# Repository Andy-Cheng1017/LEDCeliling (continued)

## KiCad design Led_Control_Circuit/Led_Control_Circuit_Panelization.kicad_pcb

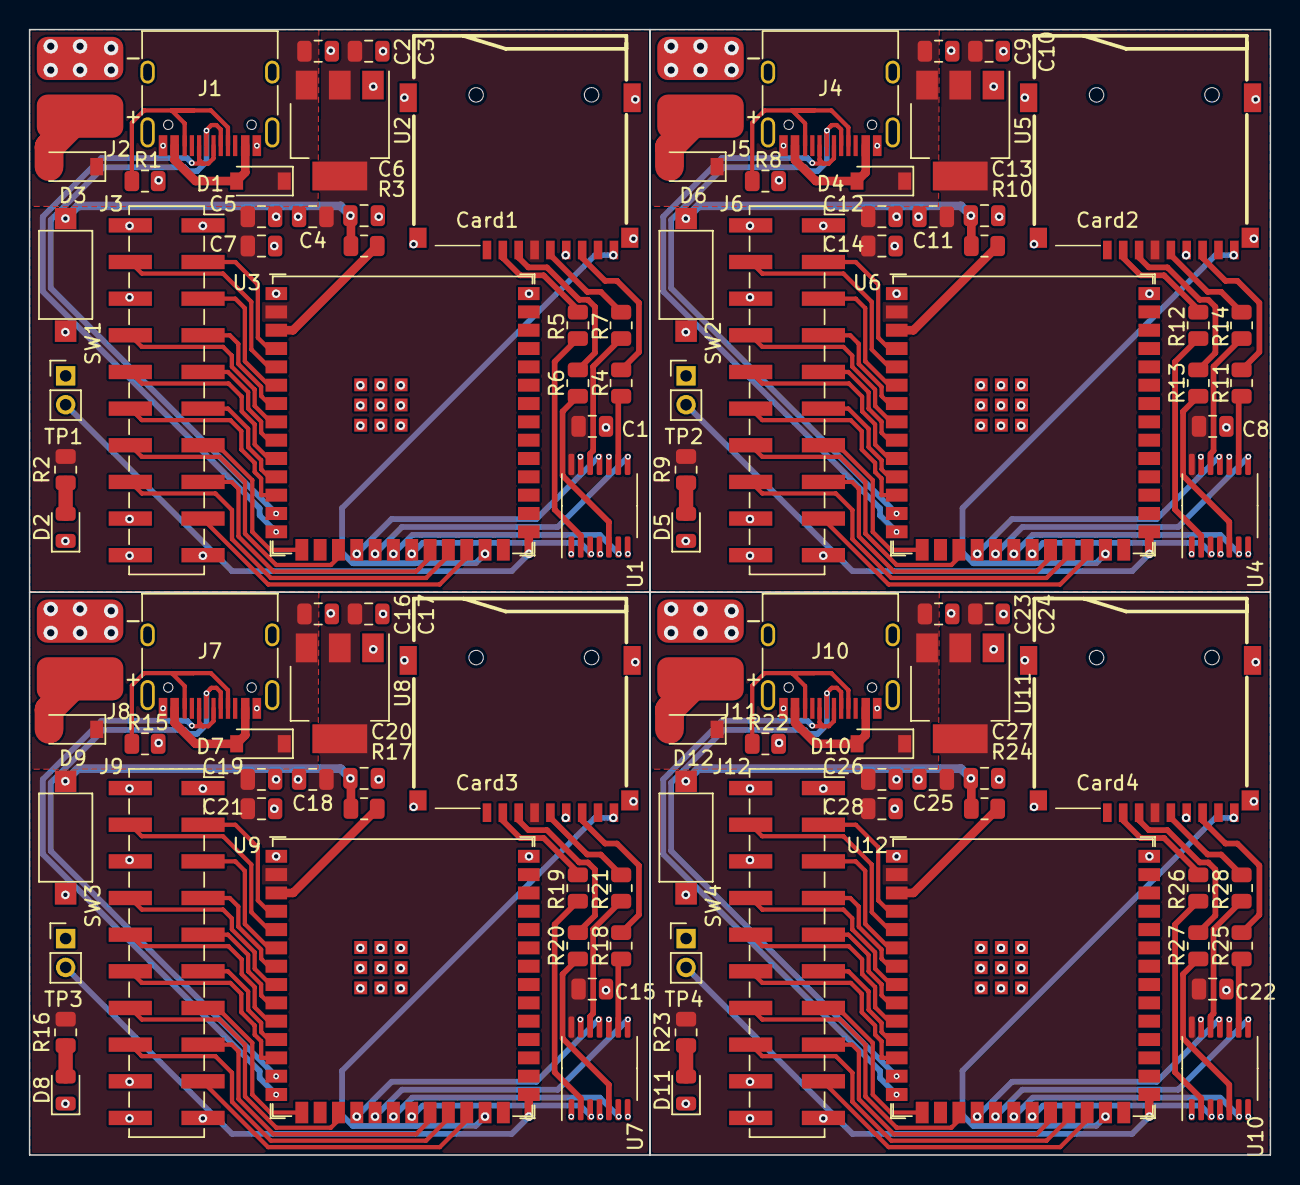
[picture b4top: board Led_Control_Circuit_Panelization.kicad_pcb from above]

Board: 2 copper layers, 86.0 x 78.0 mm, 104 parts (0 on the bottom side), 39 nets.

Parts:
C1, C7, C8, C14, C15, C21, C22, C28: 0.1u; C_0805_2012Metric
C2, C3, C5, C6, C9, C10, C12, C13, C16, C17, C19, C20, C23, C24, C26, C27: 1u; C_0805_2012Metric
C4, C11, C18, C25: 10u; C_0805_2012Metric
Card1, Card2, Card3, Card4: TF-01A; TF-SMD_TF-01A
D1, D3, D4, D6, D7, D9, D10, D12: 1N5819HW; D_SOD-123
D2, D5, D8, D11: LED0805; LED_0805_2012Metric
J1, J4, J7, J10: USB_C_Receptacle_USB2.0; USB_C_Receptacle_HRO_TYPE-C-31-M-12
J2, J5, J8, J11: Conn_01x02; Battery
J3, J6, J9, J12: Conn_01x20; PinSocket_2x10_P2.54mm_Vertical_SMD
R1, R8, R15, R22: 5.1K; R_0805_2012Metric
R2, R9, R16, R23: 1k; R_0805_2012Metric
R3, R10, R17, R24: 1K; R_0805_2012Metric
R4, R5, R6, R7, R11, R12, R13, R14, R18, R19, R20, R21, R25, R26, R27, R28: 3.3K; R_0805_2012Metric
SW1, SW2, SW3, SW4: SW_Push; SW_SPST_CK_RS282G05A3
TP1, TP2, TP3, TP4: TestPoint_2Pole; PinHeader_1x02_P2.00mm_Vertical
U1, U4, U7, U10: 74LVC125; TSSOP-14_4.4x5mm_P0.65mm
U2, U5, U8, U11: AMS1117-3.3; SOT-223-3_TabPin2
U3, U6, U9, U12: ESP32-S3-WROOM-1; ESP32-S3-WROOM-1U

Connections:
+3.3V: C1.1, C3.1, C4.1, C5.1, C7.1, C8.1, C10.1, C11.1, C12.1, C14.1, C15.1, C17.1, C18.1, C19.1, C21.1, C22.1, C24.1, C25.1, C26.1, C28.1, Card1.4 (VDD), Card2.4 (VDD), Card3.4 (VDD), Card4.4 (VDD), R2.2, R9.2, R16.2, R23.2, U1.14 (VCC), U2.2 (VO), U3.2 (3V3), U4.14 (VCC), U5.2 (VO), U6.2 (3V3), U7.14 (VCC), U8.2 (VO), U9.2 (3V3), U10.14 (VCC), U11.2 (VO), U12.2 (3V3)
+5V: C2.1, C9.1, C16.1, C23.1, D1.1 (K), D3.1 (K), D4.1 (K), D6.1 (K), D7.1 (K), D9.1 (K), D10.1 (K), D12.1 (K), U2.3 (VI), U5.3 (VI), U8.3 (VI), U11.3 (VI)
/A: J3.11, J6.11, J9.11, J12.11, U3.11 (GPIO18/U1RXD/ADC2_CH7/CLK_OUT3), U6.11 (GPIO18/U1RXD/ADC2_CH7/CLK_OUT3), U9.11 (GPIO18/U1RXD/ADC2_CH7/CLK_OUT3), U12.11 (GPIO18/U1RXD/ADC2_CH7/CLK_OUT3)
/B: J3.12, J6.12, J9.12, J12.12, U3.12 (GPIO8/TOUCH8/ADC1_CH7/SUBSPICS1), U6.12 (GPIO8/TOUCH8/ADC1_CH7/SUBSPICS1), U9.12 (GPIO8/TOUCH8/ADC1_CH7/SUBSPICS1), U12.12 (GPIO8/TOUCH8/ADC1_CH7/SUBSPICS1)
/B1: J3.5, J6.5, J9.5, J12.5, U3.6 (GPIO6/TOUCH6/ADC1_CH5), U6.6 (GPIO6/TOUCH6/ADC1_CH5), U9.6 (GPIO6/TOUCH6/ADC1_CH5), U12.6 (GPIO6/TOUCH6/ADC1_CH5)
/B2: J3.9, J6.9, J9.9, J12.9, U3.9 (GPIO16/U0CTS/ADC2_CH5/XTAL_32K_NH5), U6.9 (GPIO16/U0CTS/ADC2_CH5/XTAL_32K_NH5), U9.9 (GPIO16/U0CTS/ADC2_CH5/XTAL_32K_NH5), U12.9 (GPIO16/U0CTS/ADC2_CH5/XTAL_32K_NH5)
/C: J3.13, J6.13, J9.13, J12.13, U3.15 (GPIO3/TOUCH3/ADC1_CH2), U6.15 (GPIO3/TOUCH3/ADC1_CH2), U9.15 (GPIO3/TOUCH3/ADC1_CH2), U12.15 (GPIO3/TOUCH3/ADC1_CH2)
/CD: Card1.9 (CD), Card2.9 (CD), Card3.9 (CD), Card4.9 (CD), U3.25 (GPIO48/SPICLK_N/SUBSPICLK_N_DIFF), U6.25 (GPIO48/SPICLK_N/SUBSPICLK_N_DIFF), U9.25 (GPIO48/SPICLK_N/SUBSPICLK_N_DIFF), U12.25 (GPIO48/SPICLK_N/SUBSPICLK_N_DIFF)
/CLK: J3.15, J6.15, J9.15, J12.15, U3.22 (GPIO14/TOUCH14/ADC2_CH3/FSPIWP/FSPIDQS/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), U6.22 (GPIO14/TOUCH14/ADC2_CH3/FSPIWP/FSPIDQS/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), U9.22 (GPIO14/TOUCH14/ADC2_CH3/FSPIWP/FSPIDQS/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), U12.22 (GPIO14/TOUCH14/ADC2_CH3/FSPIWP/FSPIDQS/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)
/CS: U1.6, U3.20 (GPIO12/TOUCH12/ADC2_CH1/FSPICLK/FSPIIO6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), U4.6, U6.20 (GPIO12/TOUCH12/ADC2_CH1/FSPICLK/FSPIIO6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), U7.6, U9.20 (GPIO12/TOUCH12/ADC2_CH1/FSPICLK/FSPIIO6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), U10.6, U12.20 (GPIO12/TOUCH12/ADC2_CH1/FSPICLK/FSPIIO6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)
/D: J3.14, J6.14, J9.14, J12.14, U3.17 (GPIO9/TOUCH9/ADC1_CH8/FSPIHD/SUBSPIHD), U6.17 (GPIO9/TOUCH9/ADC1_CH8/FSPIHD/SUBSPIHD), U9.17 (GPIO9/TOUCH9/ADC1_CH8/FSPIHD/SUBSPIHD), U12.17 (GPIO9/TOUCH9/ADC1_CH8/FSPIHD/SUBSPIHD)
/D+: J1.A6 (D+), J1.B6 (D+), J4.A6 (D+), J4.B6 (D+), J7.A6 (D+), J7.B6 (D+), J10.A6 (D+), J10.B6 (D+), U3.14 (GPIO20/U1CTS/ADC2_CH9/CLK_OUT1/USB_D+), U6.14 (GPIO20/U1CTS/ADC2_CH9/CLK_OUT1/USB_D+), U9.14 (GPIO20/U1CTS/ADC2_CH9/CLK_OUT1/USB_D+), U12.14 (GPIO20/U1CTS/ADC2_CH9/CLK_OUT1/USB_D+)
/D-: J1.A7 (D-), J1.B7 (D-), J4.A7 (D-), J4.B7 (D-), J7.A7 (D-), J7.B7 (D-), J10.A7 (D-), J10.B7 (D-), U3.13 (GPIO19/U1RTS/ADC2_CH8/CLK_OUT2/USB_D-), U6.13 (GPIO19/U1RTS/ADC2_CH8/CLK_OUT2/USB_D-), U9.13 (GPIO19/U1RTS/ADC2_CH8/CLK_OUT2/USB_D-), U12.13 (GPIO19/U1RTS/ADC2_CH8/CLK_OUT2/USB_D-)
/E: J3.10, J6.10, J9.10, J12.10, U3.10 (GPIO17/U1TXD/ADC2_CH6), U6.10 (GPIO17/U1TXD/ADC2_CH6), U9.10 (GPIO17/U1TXD/ADC2_CH6), U12.10 (GPIO17/U1TXD/ADC2_CH6)
/G1: J3.4, J6.4, J9.4, J12.4, U3.5 (GPIO5/TOUCH5/ADC1_CH4), U6.5 (GPIO5/TOUCH5/ADC1_CH4), U9.5 (GPIO5/TOUCH5/ADC1_CH4), U12.5 (GPIO5/TOUCH5/ADC1_CH4)
/G2: J3.8, J6.8, J9.8, J12.8, U3.8 (GPIO15/U0RTS/ADC2_CH4/XTAL_32K_P), U6.8 (GPIO15/U0RTS/ADC2_CH4/XTAL_32K_P), U9.8 (GPIO15/U0RTS/ADC2_CH4/XTAL_32K_P), U12.8 (GPIO15/U0RTS/ADC2_CH4/XTAL_32K_P)
/LAT: J3.16, J6.16, J9.16, J12.16, U3.23 (GPIO21), U6.23 (GPIO21), U9.23 (GPIO21), U12.23 (GPIO21)
/MISO: U1.3, U3.21 (GPIO13/TOUCH13/ADC2_CH2/FSPIQ/FSPIIO7/S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), U4.3, U6.21 (GPIO13/TOUCH13/ADC2_CH2/FSPIQ/FSPIIO7/S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), U7.3, U9.21 (GPIO13/TOUCH13/ADC2_CH2/FSPIQ/FSPIIO7/S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), U10.3, U12.21 (GPIO13/TOUCH13/ADC2_CH2/FSPIQ/FSPIIO7/S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)
/MOSI: U1.8, U3.19 (GPIO11/TOUCH11/ADC2_CH0/FSPID/FSPIIO5/S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), U4.8, U6.19 (GPIO11/TOUCH11/ADC2_CH0/FSPID/FSPIIO5/S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), U7.8, U9.19 (GPIO11/TOUCH11/ADC2_CH0/FSPID/FSPIIO5/S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), U10.8, U12.19 (GPIO11/TOUCH11/ADC2_CH0/FSPID/FSPIIO5/S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)
/OE: J3.17, J6.17, J9.17, J12.17, U3.24 (GPIO47/SPICLK_P/SUBSPICLK_P_DIFF), U6.24 (GPIO47/SPICLK_P/SUBSPICLK_P_DIFF), U9.24 (GPIO47/SPICLK_P/SUBSPICLK_P_DIFF), U12.24 (GPIO47/SPICLK_P/SUBSPICLK_P_DIFF)
/R1: J3.3, J6.3, J9.3, J12.3, U3.4 (GPIO4/TOUCH4/ADC1_CH3), U6.4 (GPIO4/TOUCH4/ADC1_CH3), U9.4 (GPIO4/TOUCH4/ADC1_CH3), U12.4 (GPIO4/TOUCH4/ADC1_CH3)
/R2: J3.7, J6.7, J9.7, J12.7, U3.7 (GPIO7/TOUCH7/ADC1_CH6), U6.7 (GPIO7/TOUCH7/ADC1_CH6), U9.7 (GPIO7/TOUCH7/ADC1_CH6), U12.7 (GPIO7/TOUCH7/ADC1_CH6)
/SCK: U1.11, U3.18 (GPIO10/TOUCH10/ADC1_CH9/FSPICS0/FSPIIO4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), U4.11, U6.18 (GPIO10/TOUCH10/ADC1_CH9/FSPICS0/FSPIIO4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), U7.11, U9.18 (GPIO10/TOUCH10/ADC1_CH9/FSPICS0/FSPIIO4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), U10.11, U12.18 (GPIO10/TOUCH10/ADC1_CH9/FSPICS0/FSPIIO4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)
GND: C1.2, C2.2, C3.2, C4.2, C5.2, C6.1, C7.2, C8.2, C9.2, C10.2, C11.2, C12.2, C13.1, C14.2, C15.2, C16.2, C17.2, C18.2, C19.2, C20.1, C21.2, C22.2, C23.2, C24.2, C25.2, C26.2, C27.1, C28.2, Card1.6 (VSS), Card1.10 (GND), Card1.11 (GND), Card1.12 (GND), Card1.13 (GND), Card2.6 (VSS), Card2.10 (GND), Card2.11 (GND), Card2.12 (GND), Card2.13 (GND), Card3.6 (VSS), Card3.10 (GND), Card3.11 (GND), Card3.12 (GND), Card3.13 (GND), Card4.6 (VSS), Card4.10 (GND), Card4.11 (GND), Card4.12 (GND), Card4.13 (GND), D2.1 (K), D5.1 (K), D8.1 (K), D11.1 (K), J1.A1 (GND), J1.A12 (GND), J1.B1 (GND), J1.B12 (GND), J1.S1 (SHIELD), J2.2, J3.1, J3.2, J3.6, J3.18, J3.19, J3.20, J4.A1 (GND), J4.A12 (GND), J4.B1 (GND), J4.B12 (GND), J4.S1 (SHIELD), J5.2, J6.1, J6.2, J6.6, J6.18, J6.19, J6.20, J7.A1 (GND), J7.A12 (GND), J7.B1 (GND), J7.B12 (GND), J7.S1 (SHIELD), J8.2, J9.1, J9.2, J9.6, J9.18, J9.19, J9.20, J10.A1 (GND), J10.A12 (GND), J10.B1 (GND), J10.B12 (GND), J10.S1 (SHIELD), J11.2, J12.1, J12.2, J12.6, J12.18, J12.19, J12.20, R1.2, R8.2, R15.2, R22.2, SW1.1, SW2.1, SW3.1, SW4.1, TP1.1, TP2.1, TP3.1, TP4.1, U1.1, U1.4, U1.7 (GND), U1.10, U1.13, U2.1 (GND), U3.1 (GND), U3.40 (GND), U3.41 (GND), U4.1, U4.4, U4.7 (GND), U4.10, U4.13, U5.1 (GND), U6.1 (GND), U6.40 (GND), U6.41 (GND), U7.1, U7.4, U7.7 (GND), U7.10, U7.13, U8.1 (GND), U9.1 (GND), U9.40 (GND), U9.41 (GND), U10.1, U10.4, U10.7 (GND), U10.10, U10.13, U11.1 (GND), U12.1 (GND), U12.40 (GND), U12.41 (GND)
unnamed: C6.2, C13.2, C20.2, C27.2, R3.1, R10.1, R17.1, R24.1, SW1.2, SW2.2, SW3.2, SW4.2
unnamed: Card1.2 (CDDAT3(CS)), Card2.2 (CDDAT3(CS)), Card3.2 (CDDAT3(CS)), Card4.2 (CDDAT3(CS)), R5.1, R12.1, R19.1, R26.1
unnamed: Card1.3 (CMD(DI)), Card2.3 (CMD(DI)), Card3.3 (CMD(DI)), Card4.3 (CMD(DI)), R6.1, R13.1, R20.1, R27.1
unnamed: Card1.5 (CLK(SCLK)), Card2.5 (CLK(SCLK)), Card3.5 (CLK(SCLK)), Card4.5 (CLK(SCLK)), R7.1, R14.1, R21.1, R28.1
unnamed: Card1.7 (DAT0(D0)), Card2.7 (DAT0(D0)), Card3.7 (DAT0(D0)), Card4.7 (DAT0(D0)), R4.1, R11.1, R18.1, R25.1
unnamed: D1.2 (A), D4.2 (A), D7.2 (A), D10.2 (A), J1.A4 (VBUS), J1.A9 (VBUS), J1.B4 (VBUS), J1.B9 (VBUS), J4.A4 (VBUS), J4.A9 (VBUS), J4.B4 (VBUS), J4.B9 (VBUS), J7.A4 (VBUS), J7.A9 (VBUS), J7.B4 (VBUS), J7.B9 (VBUS), J10.A4 (VBUS), J10.A9 (VBUS), J10.B4 (VBUS), J10.B9 (VBUS)
unnamed: D2.2 (A), D5.2 (A), D8.2 (A), D11.2 (A), R2.1, R9.1, R16.1, R23.1
unnamed: D3.2 (A), D6.2 (A), D9.2 (A), D12.2 (A), J2.1, J5.1, J8.1, J11.1
unnamed: J1.A5 (CC1), J1.B5 (CC2), J4.A5 (CC1), J4.B5 (CC2), J7.A5 (CC1), J7.B5 (CC2), J10.A5 (CC1), J10.B5 (CC2), R1.1, R8.1, R15.1, R22.1
unnamed: R3.2, R10.2, R17.2, R24.2, U3.3 (EN), U6.3 (EN), U9.3 (EN), U12.3 (EN)
unnamed: R4.2, R11.2, R18.2, R25.2, U1.9, U4.9, U7.9, U10.9
unnamed: R5.2, R12.2, R19.2, R26.2, U1.2, U4.2, U7.2, U10.2
unnamed: R6.2, R13.2, R20.2, R27.2, U1.5, U4.5, U7.5, U10.5
unnamed: R7.2, R14.2, R21.2, R28.2, U1.12, U4.12, U7.12, U10.12
unnamed: TP1.2, TP2.2, TP3.2, TP4.2, U3.27 (GPIO0/BOOT), U6.27 (GPIO0/BOOT), U9.27 (GPIO0/BOOT), U12.27 (GPIO0/BOOT)

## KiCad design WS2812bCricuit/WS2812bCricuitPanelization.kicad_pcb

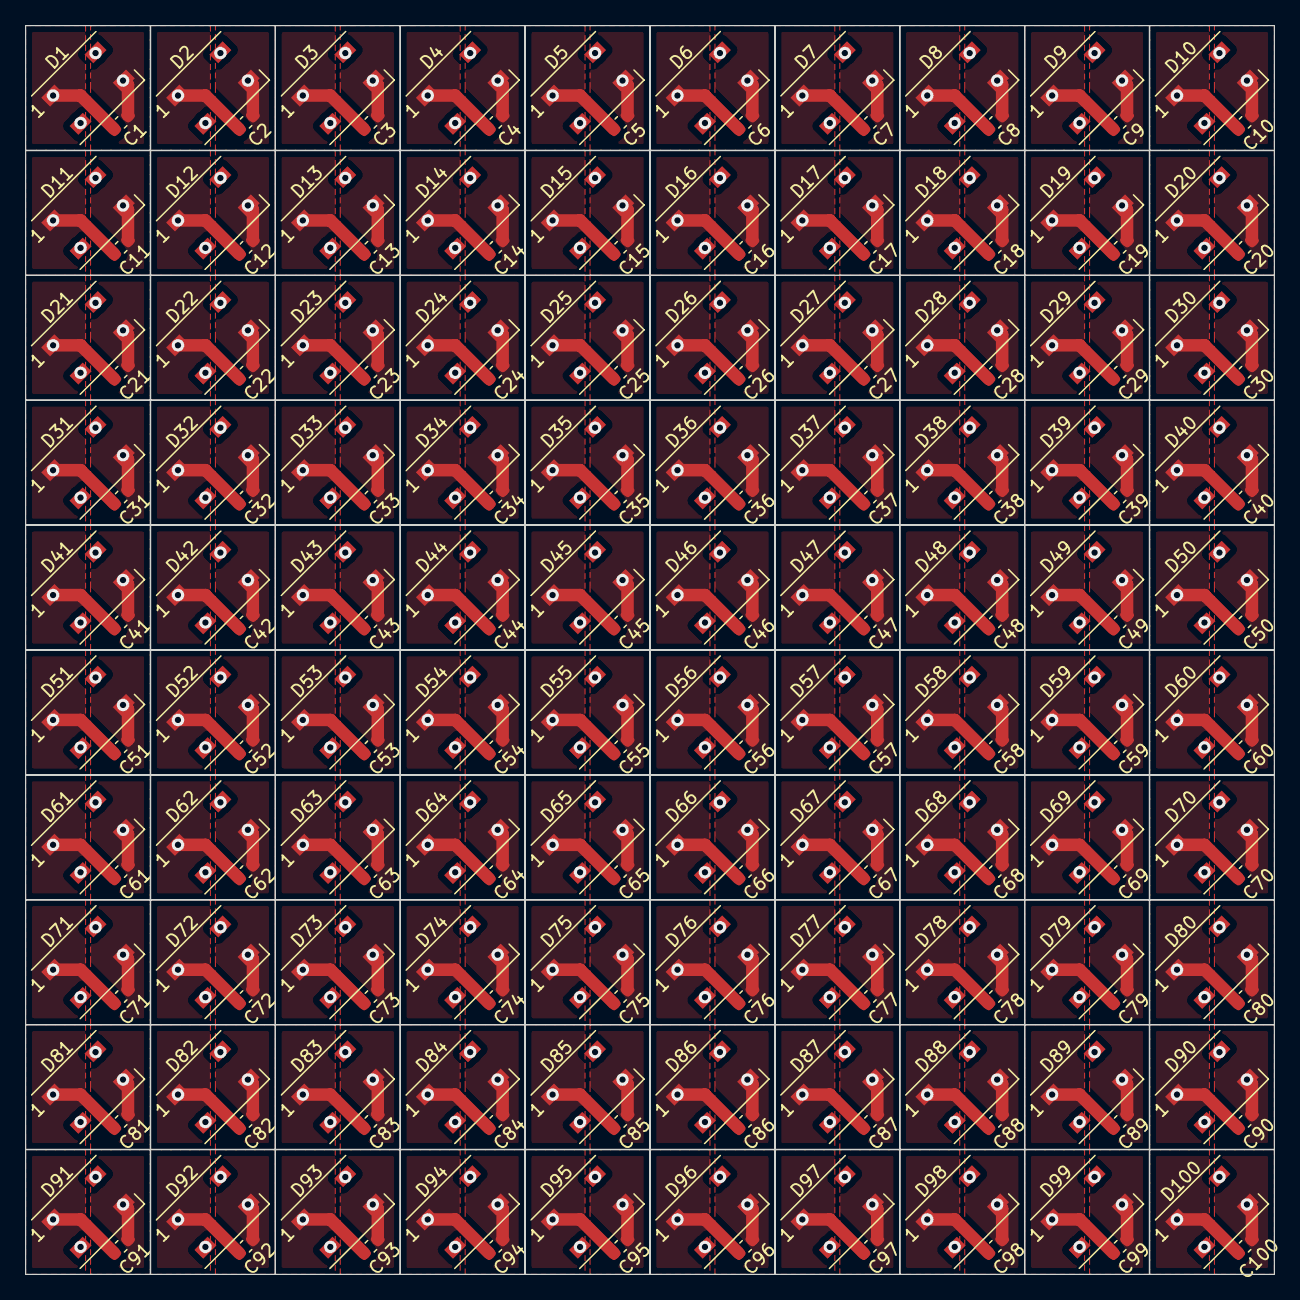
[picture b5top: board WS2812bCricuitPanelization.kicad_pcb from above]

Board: 2 copper layers, 100.0 x 100.0 mm, 200 parts (0 on the bottom side), 2 nets.

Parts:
C1, C2, C3, C4, C5, C6, C7, C8, C9, C10, C11, C12, C13, C14, C15, C16, C17, C18, C19, C20, C21, C22, C23, C24, C25, C26, C27, C28, C29, C30, C31, C32, C33, C34, C35, C36, C37, C38, C39, C40, C41, C42, C43, C44, C45, C46, C47, C48, C49, C50, C51, C52, C53, C54, C55, C56, C57, C58, C59, C60, C61, C62, C63, C64, C65, C66, C67, C68, C69, C70, C71, C72, C73, C74, C75, C76, C77, C78, C79, C80, C81, C82, C83, C84, C85, C86, C87, C88, C89, C90, C91, C92, C93, C94, C95, C96, C97, C98, C99, C100: C; C_0603_1608Metric
D1, D2, D3, D4, D5, D6, D7, D8, D9, D10, D11, D12, D13, D14, D15, D16, D17, D18, D19, D20, D21, D22, D23, D24, D25, D26, D27, D28, D29, D30, D31, D32, D33, D34, D35, D36, D37, D38, D39, D40, D41, D42, D43, D44, D45, D46, D47, D48, D49, D50, D51, D52, D53, D54, D55, D56, D57, D58, D59, D60, D61, D62, D63, D64, D65, D66, D67, D68, D69, D70, D71, D72, D73, D74, D75, D76, D77, D78, D79, D80, D81, D82, D83, D84, D85, D86, D87, D88, D89, D90, D91, D92, D93, D94, D95, D96, D97, D98, D99, D100: WS2812B; LED_WS2812B_PLCC4_5.0x5.0mm_P3.2mm

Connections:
unnamed: C1.1, C2.1, C3.1, C4.1, C5.1, C6.1, C7.1, C8.1, C9.1, C10.1, C11.1, C12.1, C13.1, C14.1, C15.1, C16.1, C17.1, C18.1, C19.1, C20.1, C21.1, C22.1, C23.1, C24.1, C25.1, C26.1, C27.1, C28.1, C29.1, C30.1, C31.1, C32.1, C33.1, C34.1, C35.1, C36.1, C37.1, C38.1, C39.1, C40.1, C41.1, C42.1, C43.1, C44.1, C45.1, C46.1, C47.1, C48.1, C49.1, C50.1, C51.1, C52.1, C53.1, C54.1, C55.1, C56.1, C57.1, C58.1, C59.1, C60.1, C61.1, C62.1, C63.1, C64.1, C65.1, C66.1, C67.1, C68.1, C69.1, C70.1, C71.1, C72.1, C73.1, C74.1, C75.1, C76.1, C77.1, C78.1, C79.1, C80.1, C81.1, C82.1, C83.1, C84.1, C85.1, C86.1, C87.1, C88.1, C89.1, C90.1, C91.1, C92.1, C93.1, C94.1, C95.1, C96.1, C97.1, C98.1, C99.1, C100.1, D1.1 (VDD), D2.1 (VDD), D3.1 (VDD), D4.1 (VDD), D5.1 (VDD), D6.1 (VDD), D7.1 (VDD), D8.1 (VDD), D9.1 (VDD), D10.1 (VDD), D11.1 (VDD), D12.1 (VDD), D13.1 (VDD), D14.1 (VDD), D15.1 (VDD), D16.1 (VDD), D17.1 (VDD), D18.1 (VDD), D19.1 (VDD), D20.1 (VDD), D21.1 (VDD), D22.1 (VDD), D23.1 (VDD), D24.1 (VDD), D25.1 (VDD), D26.1 (VDD), D27.1 (VDD), D28.1 (VDD), D29.1 (VDD), D30.1 (VDD), D31.1 (VDD), D32.1 (VDD), D33.1 (VDD), D34.1 (VDD), D35.1 (VDD), D36.1 (VDD), D37.1 (VDD), D38.1 (VDD), D39.1 (VDD), D40.1 (VDD), D41.1 (VDD), D42.1 (VDD), D43.1 (VDD), D44.1 (VDD), D45.1 (VDD), D46.1 (VDD), D47.1 (VDD), D48.1 (VDD), D49.1 (VDD), D50.1 (VDD), D51.1 (VDD), D52.1 (VDD), D53.1 (VDD), D54.1 (VDD), D55.1 (VDD), D56.1 (VDD), D57.1 (VDD), D58.1 (VDD), D59.1 (VDD), D60.1 (VDD), D61.1 (VDD), D62.1 (VDD), D63.1 (VDD), D64.1 (VDD), D65.1 (VDD), D66.1 (VDD), D67.1 (VDD), D68.1 (VDD), D69.1 (VDD), D70.1 (VDD), D71.1 (VDD), D72.1 (VDD), D73.1 (VDD), D74.1 (VDD), D75.1 (VDD), D76.1 (VDD), D77.1 (VDD), D78.1 (VDD), D79.1 (VDD), D80.1 (VDD), D81.1 (VDD), D82.1 (VDD), D83.1 (VDD), D84.1 (VDD), D85.1 (VDD), D86.1 (VDD), D87.1 (VDD), D88.1 (VDD), D89.1 (VDD), D90.1 (VDD), D91.1 (VDD), D92.1 (VDD), D93.1 (VDD), D94.1 (VDD), D95.1 (VDD), D96.1 (VDD), D97.1 (VDD), D98.1 (VDD), D99.1 (VDD), D100.1 (VDD)
unnamed: C1.2, C2.2, C3.2, C4.2, C5.2, C6.2, C7.2, C8.2, C9.2, C10.2, C11.2, C12.2, C13.2, C14.2, C15.2, C16.2, C17.2, C18.2, C19.2, C20.2, C21.2, C22.2, C23.2, C24.2, C25.2, C26.2, C27.2, C28.2, C29.2, C30.2, C31.2, C32.2, C33.2, C34.2, C35.2, C36.2, C37.2, C38.2, C39.2, C40.2, C41.2, C42.2, C43.2, C44.2, C45.2, C46.2, C47.2, C48.2, C49.2, C50.2, C51.2, C52.2, C53.2, C54.2, C55.2, C56.2, C57.2, C58.2, C59.2, C60.2, C61.2, C62.2, C63.2, C64.2, C65.2, C66.2, C67.2, C68.2, C69.2, C70.2, C71.2, C72.2, C73.2, C74.2, C75.2, C76.2, C77.2, C78.2, C79.2, C80.2, C81.2, C82.2, C83.2, C84.2, C85.2, C86.2, C87.2, C88.2, C89.2, C90.2, C91.2, C92.2, C93.2, C94.2, C95.2, C96.2, C97.2, C98.2, C99.2, C100.2, D1.3 (VSS), D2.3 (VSS), D3.3 (VSS), D4.3 (VSS), D5.3 (VSS), D6.3 (VSS), D7.3 (VSS), D8.3 (VSS), D9.3 (VSS), D10.3 (VSS), D11.3 (VSS), D12.3 (VSS), D13.3 (VSS), D14.3 (VSS), D15.3 (VSS), D16.3 (VSS), D17.3 (VSS), D18.3 (VSS), D19.3 (VSS), D20.3 (VSS), D21.3 (VSS), D22.3 (VSS), D23.3 (VSS), D24.3 (VSS), D25.3 (VSS), D26.3 (VSS), D27.3 (VSS), D28.3 (VSS), D29.3 (VSS), D30.3 (VSS), D31.3 (VSS), D32.3 (VSS), D33.3 (VSS), D34.3 (VSS), D35.3 (VSS), D36.3 (VSS), D37.3 (VSS), D38.3 (VSS), D39.3 (VSS), D40.3 (VSS), D41.3 (VSS), D42.3 (VSS), D43.3 (VSS), D44.3 (VSS), D45.3 (VSS), D46.3 (VSS), D47.3 (VSS), D48.3 (VSS), D49.3 (VSS), D50.3 (VSS), D51.3 (VSS), D52.3 (VSS), D53.3 (VSS), D54.3 (VSS), D55.3 (VSS), D56.3 (VSS), D57.3 (VSS), D58.3 (VSS), D59.3 (VSS), D60.3 (VSS), D61.3 (VSS), D62.3 (VSS), D63.3 (VSS), D64.3 (VSS), D65.3 (VSS), D66.3 (VSS), D67.3 (VSS), D68.3 (VSS), D69.3 (VSS), D70.3 (VSS), D71.3 (VSS), D72.3 (VSS), D73.3 (VSS), D74.3 (VSS), D75.3 (VSS), D76.3 (VSS), D77.3 (VSS), D78.3 (VSS), D79.3 (VSS), D80.3 (VSS), D81.3 (VSS), D82.3 (VSS), D83.3 (VSS), D84.3 (VSS), D85.3 (VSS), D86.3 (VSS), D87.3 (VSS), D88.3 (VSS), D89.3 (VSS), D90.3 (VSS), D91.3 (VSS), D92.3 (VSS), D93.3 (VSS), D94.3 (VSS), D95.3 (VSS), D96.3 (VSS), D97.3 (VSS), D98.3 (VSS), D99.3 (VSS), D100.3 (VSS)

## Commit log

2022-09-26 Excel文件完成，小電路完成
2022-09-26 9/26更新
2022-09-27 新增控制電路
2022-09-28 新增文件
2022-11-21 fork hub75
2023-02-28 updater
